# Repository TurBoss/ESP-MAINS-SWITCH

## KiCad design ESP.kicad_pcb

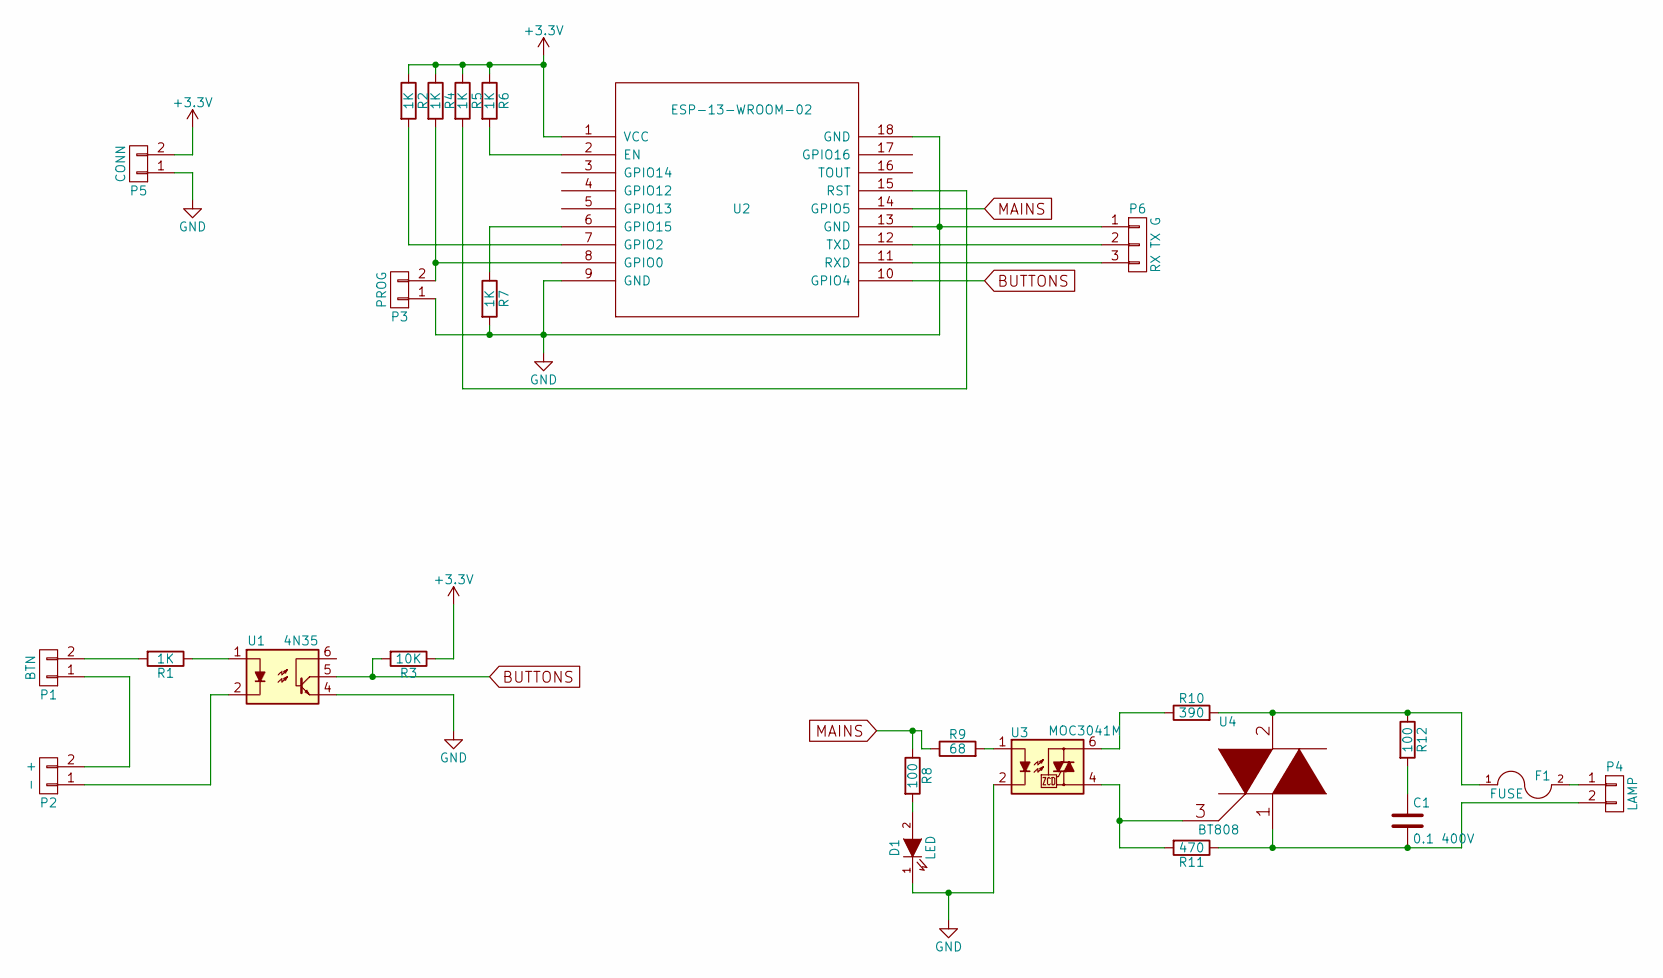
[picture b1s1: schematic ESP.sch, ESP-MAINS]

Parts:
C1: 0.1 400V; C_Rect_L18_W7_P15
D1: LED; LED-3MM
F1: FUSE; Fuseholder5x20_horiz_SemiClosed_Casing10x25mm
P1: BTN; bornier2
P2: - +; bornier2
P3: PROG; Pin_Header_Straight_1x02
P4: LAMP; bornier2
P5: CONN; bornier2
P6: RX TX G; Pin_Header_Straight_1x03
R1, R2, R4, R5, R6, R7: 1K; Resistor_Horizontal_RM10mm
R3: 10K; Resistor_Horizontal_RM10mm
R8: 100; Resistor_Horizontal_RM10mm
R9: 68; Resistor_Horizontal_RM10mm
R10: 390; Resistor_Horizontal_RM10mm
R11: 470; Resistor_Horizontal_RM10mm
R12: 100; Resistor_Horizontal_RM15mm
U1: 4N35; DIP-6__300_ELL
U2: ESP-13-WROOM-02
U3: MOC3041M; DIP-6__300_ELL
U4: BT808; TO-220_Neutral123_Vertical_LargePads

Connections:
+3V3: P5.2, R2.1, R3.1, R4.1, R5.1, R6.1, U2.1 (VCC)
BUTTONS: R3.2, U1.5, U2.10 (GPIO4)
GND: D1.1 (K), P3.1, P5.1, P6.1, R7.2, U1.4, U2.9 (GND), U2.13 (GND), U2.18 (GND), U3.2
MAINS: R8.1, R9.1, U2.14 (GPIO5)
unnamed: C1.1, R12.2
unnamed: C1.2, P4.2, R11.1, U4.1
unnamed: D1.2 (A), R8.2
unnamed: F1.1, R10.2, R12.1, U4.2
unnamed: F1.2, P4.1
unnamed: P1.1, P2.2
unnamed: P1.2, R1.2
unnamed: P2.1, U1.2
unnamed: P3.2, R4.2, U2.8 (GPIO0)
unnamed: P6.2, U2.12 (TXD)
unnamed: P6.3, U2.11 (RXD)
unnamed: R1.1, U1.1
unnamed: R2.2, U2.7 (GPIO2)
unnamed: R5.2, U2.15 (RST)
unnamed: R6.2, U2.2 (EN)
unnamed: R7.1, U2.6 (GPIO15)
unnamed: R9.2, U3.1
unnamed: R10.1, U3.6
unnamed: R11.2, U3.4, U4.3

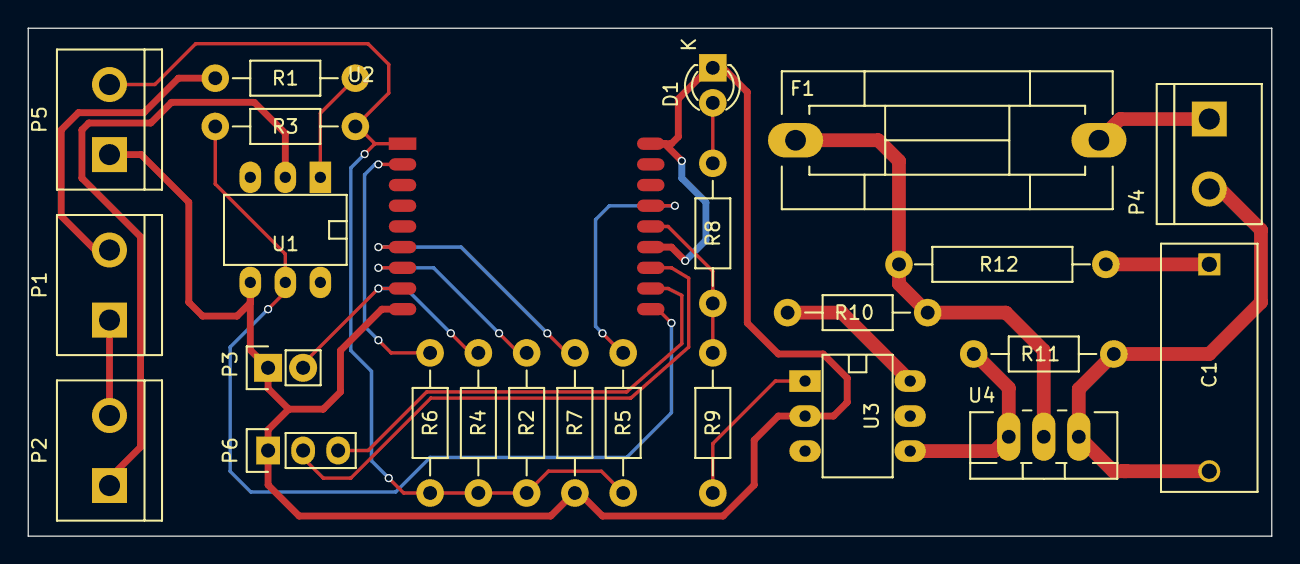
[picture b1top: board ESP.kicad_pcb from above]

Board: 2 copper layers, 90.2 x 36.8 mm, 25 parts (0 on the bottom side), 23 nets.

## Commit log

2015-10-12 PCB redistribution
2015-10-12 PCB Wiring
2015-10-12 PCB Edjes
2015-10-12 Gerber files
